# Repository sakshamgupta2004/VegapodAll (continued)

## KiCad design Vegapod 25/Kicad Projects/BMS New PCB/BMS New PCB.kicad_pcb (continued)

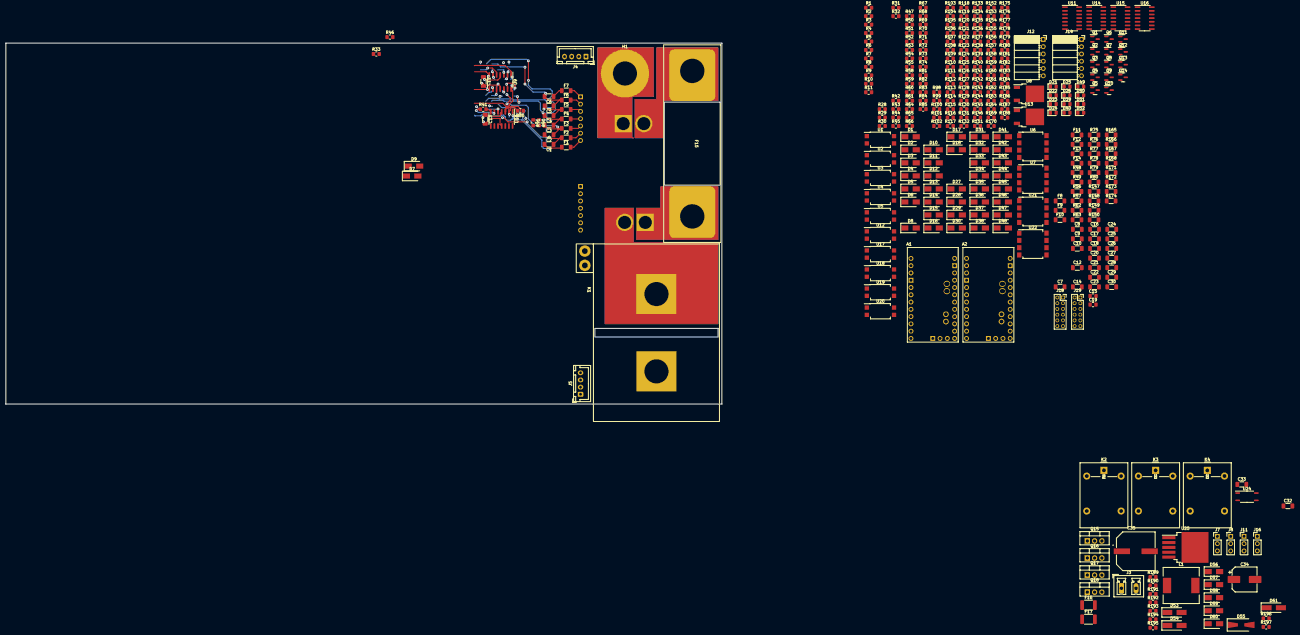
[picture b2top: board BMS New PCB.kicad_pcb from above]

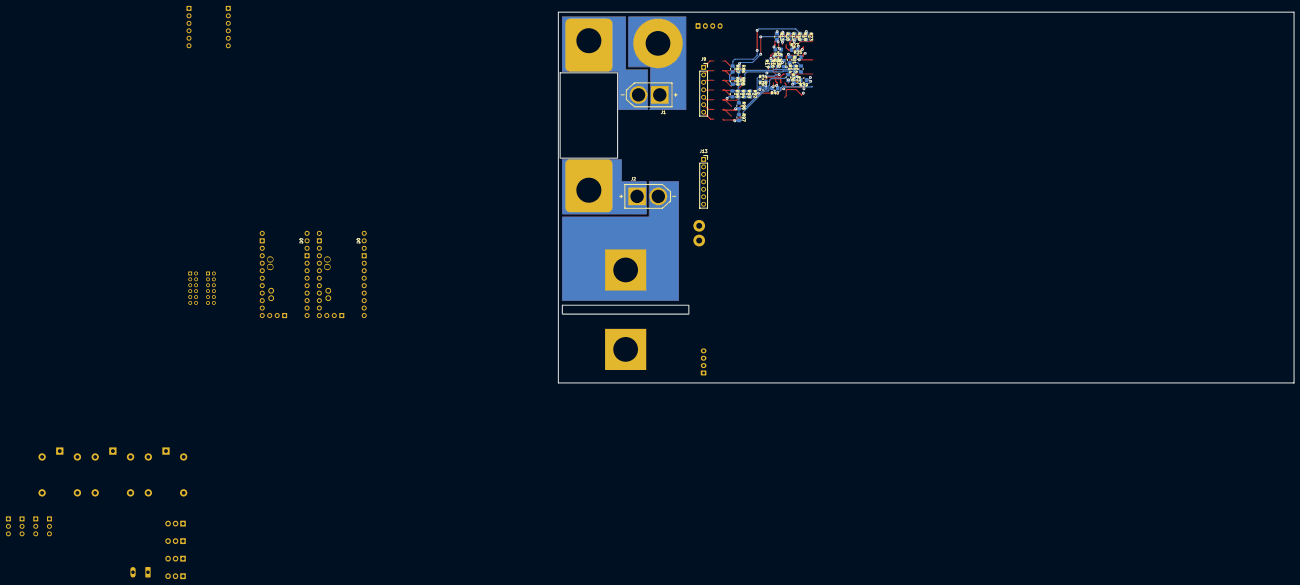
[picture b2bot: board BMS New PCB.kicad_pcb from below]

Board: 4 copper layers, 250.0 x 126.0 mm, 372 parts (36 on the bottom side), 238 nets.

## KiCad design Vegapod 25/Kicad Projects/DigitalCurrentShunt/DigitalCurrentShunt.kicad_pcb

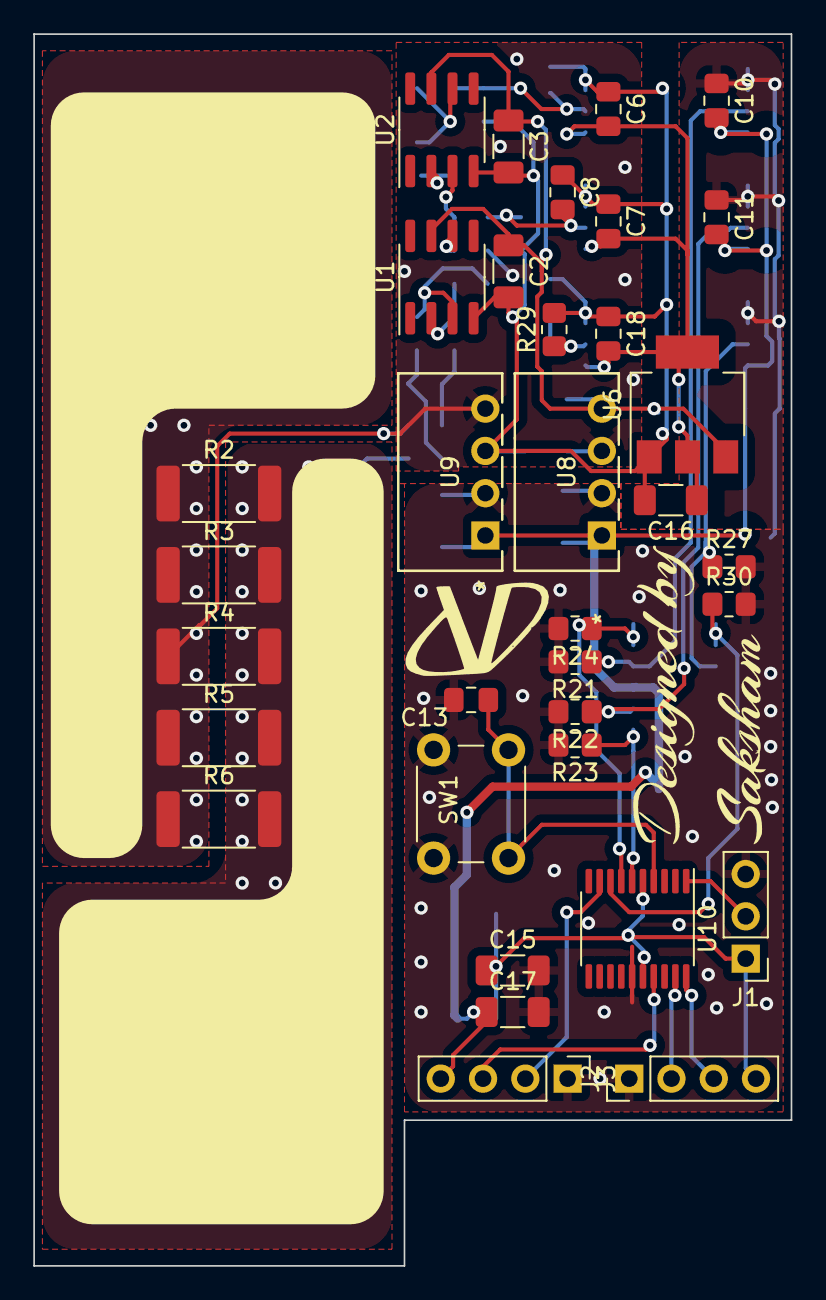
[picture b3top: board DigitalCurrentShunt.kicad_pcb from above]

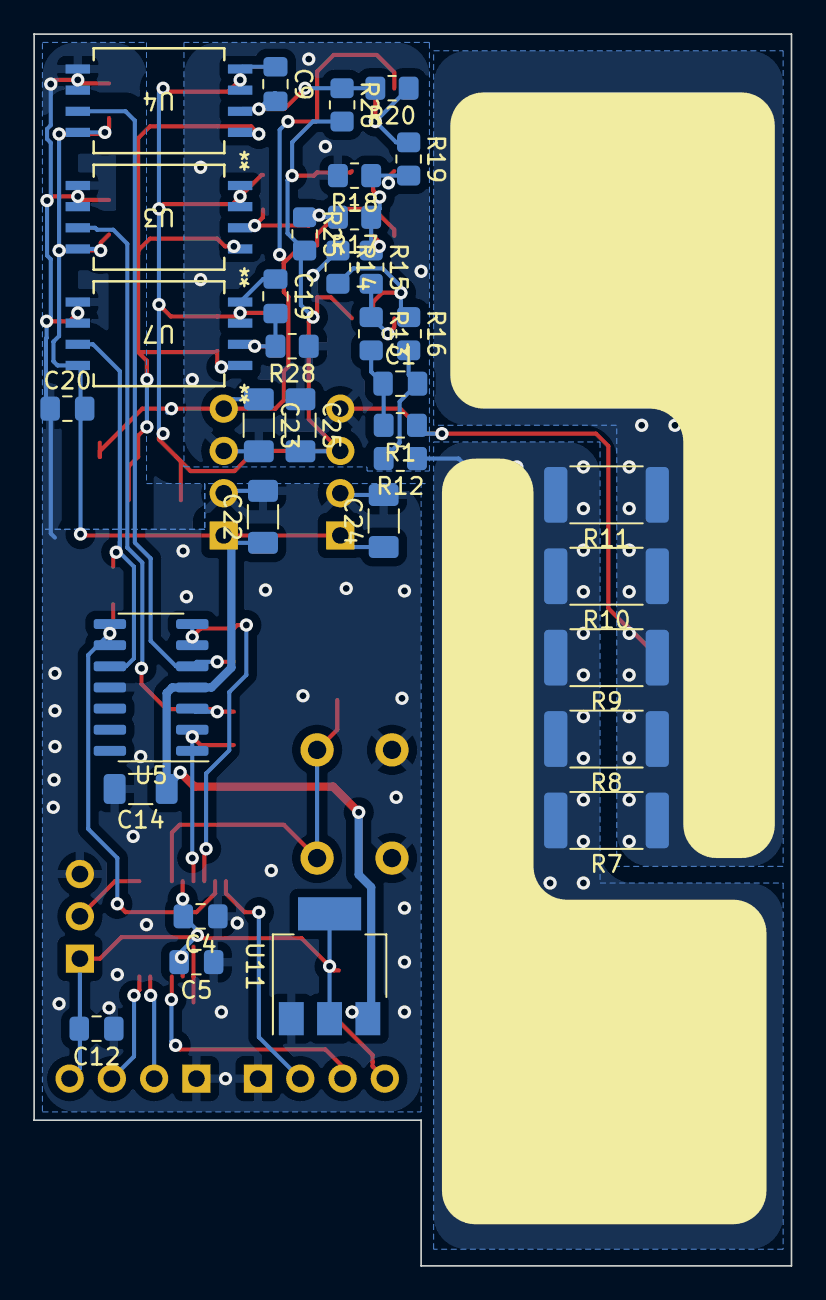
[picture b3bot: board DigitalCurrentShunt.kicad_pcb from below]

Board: 4 copper layers, 45.5 x 74.0 mm, 71 parts (35 on the bottom side), 30 nets.

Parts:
C1, C4, C5, C6, C7, C10, C11, C12, C13, C18, C20: 100n; C_0805_2012Metric_Pad1.18x1.45mm_HandSolder
C2, C3, C14, C15, C16, C17, C22, C23, C24, C25: 10uF; C_1206_3216Metric_Pad1.33x1.80mm_HandSolder
C8, C9, C19: 10n; C_0805_2012Metric_Pad1.18x1.45mm_HandSolder
J1: BootSel; PinHeader_1x03_P2.54mm_Vertical
J2: STLINK; PinHeader_1x04_P2.54mm_Vertical
J3: UART; PinHeader_1x04_P2.54mm_Vertical
MP1, MP2: 7461059; WP-BUCF_7461059
R1, R12: 47; R_0805_2012Metric_Pad1.20x1.40mm_HandSolder
R2, R3, R4, R5, R6, R7, R8, R9, R10, R11: 5mOhm; R_2512_6332Metric_Pad1.40x3.35mm_HandSolder
R13, R16, R17, R18, R20, R23, R24, R25, R26, R28, R29, R30: 470; R_0805_2012Metric_Pad1.20x1.40mm_HandSolder
R14, R15: 22k; R_0805_2012Metric_Pad1.20x1.40mm_HandSolder
R19, R21, R22, R27: 4.7k; R_0805_2012Metric_Pad1.20x1.40mm_HandSolder
SW1: SW_Push; SW_PUSH_6mm
U1, U2: OP177; SOIC-8_3.9x4.9mm_P1.27mm
U3, U4, U7: ADUM4195-1BRIZ; RI-8-1_ADI
U5: LM324; SOIC-14_3.9x8.7mm_P1.27mm
U6: AMS1117-5.0; SOT-223-3_TabPin2
U8, U9: B0505S-1WR3; B0505S_MNS
U10: STM32F030F4Px; TSSOP-20_4.4x6.5mm_P0.65mm
U11: AMS1117-3.3; SOT-223-3_TabPin2

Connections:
+3.3V: C4.2, C5.2, C12.2, C15.1, J1.1, J2.4, U10.5 (VDDA), U10.16 (VDD), U11.2 (VO)
+5V: C2.1, C3.1, C23.1, U1.7 (V+), U2.7 (V+), U6.3 (VI), U8.4 (+VO)
+5VD: C10.2, C11.2, C14.1, C17.1, C20.2, C22.1, C24.1, J3.4, U3.8 (VDD1), U4.8 (VDD1), U5.4 (V+), U7.8 (VDD1), U8.1 (GND), U9.1 (GND), U11.3 (VI)
-5V: C2.2, C3.2, C6.1, C7.1, C8.1, C9.1, C16.2, C18.1, C19.1, C25.2, R25.2, R26.2, R29.2, U1.4 (V-), U2.4 (V-), U3.3 (SHTD), U3.4 (GND2), U4.3 (SHTD), U4.4 (GND2), U6.1 (GND), U7.3 (SHTD), U7.4 (GND2), U9.3 (0V)
-BATT: C23.2, C25.1, MP1.1, R1.1, R2.1, R3.1, R4.1, R5.1, R6.1, R7.1, R8.1, R9.1, R10.1, R11.1, R14.1, R18.2, R28.1, U8.3 (0V), U9.4 (+VO)
/RST: C13.2, SW1.2, U10.4 (NRST)
A0: C8.2, R17.2, R25.1, U3.2 (VIN)
A1: C9.2, R20.2, R26.1, U4.2 (VIN)
GNDD: C4.1, C5.1, C10.1, C11.1, C12.1, C13.1, C14.2, C15.2, C17.2, C20.1, C22.2, C24.2, J1.3, J2.1, J3.1, R21.2, R22.2, R23.2, R24.2, R27.2, R30.2, SW1.1, U3.5 (GND1), U3.6 (NC), U4.5 (GND1), U4.6 (NC), U5.11 (V-), U7.5 (GND1), U7.6 (NC), U8.2 (VIN), U9.2 (VIN), U10.15 (VSS), U11.1 (GND)
unnamed: C1.1, R1.2, R13.2
unnamed: C1.2, R12.2, R16.2
unnamed: J1.2, U10.1 (BOOT0)
unnamed: MP2.1, R2.2, R3.2, R4.2, R5.2, R6.2, R7.2, R8.2, R9.2, R10.2, R11.2, R12.1
unnamed: R19.1, R20.1, U2.6
unnamed: R14.2, R16.1, U1.3 (+)
unnamed: R13.1, R15.2, U1.2 (-)
unnamed: R15.1, R17.1, U1.6, U2.3 (+)
unnamed: R18.1, R19.2, U2.2 (-)
unnamed: C6.2, C7.2, C16.1, C18.2, U3.1 (VDD2), U4.1 (VDD2), U6.2 (VO), U7.1 (VDD2)
unnamed: R22.1, U3.7 (VOUT), U5.3 (+)
unnamed: R21.1, U4.7 (VOUT), U5.5 (+)
unnamed: R27.1, U5.10 (+), U7.7 (VOUT)
unnamed: C19.2, R28.2, R29.1, U7.2 (VIN)
PA0: R23.1, U5.1, U5.2 (-), U10.6 (PA0)
PA1: R24.1, U5.6 (-), U5.7, U10.7 (PA1)
PA2: R30.1, U5.8, U5.9 (-), U10.8 (PA2)
RX: J3.2, U10.9 (PA3)
SWCLK: J2.2, U10.19 (PA13)
SWDIO: J2.3, U10.20 (PA14)
TX: J3.3, U10.17 (PA9)

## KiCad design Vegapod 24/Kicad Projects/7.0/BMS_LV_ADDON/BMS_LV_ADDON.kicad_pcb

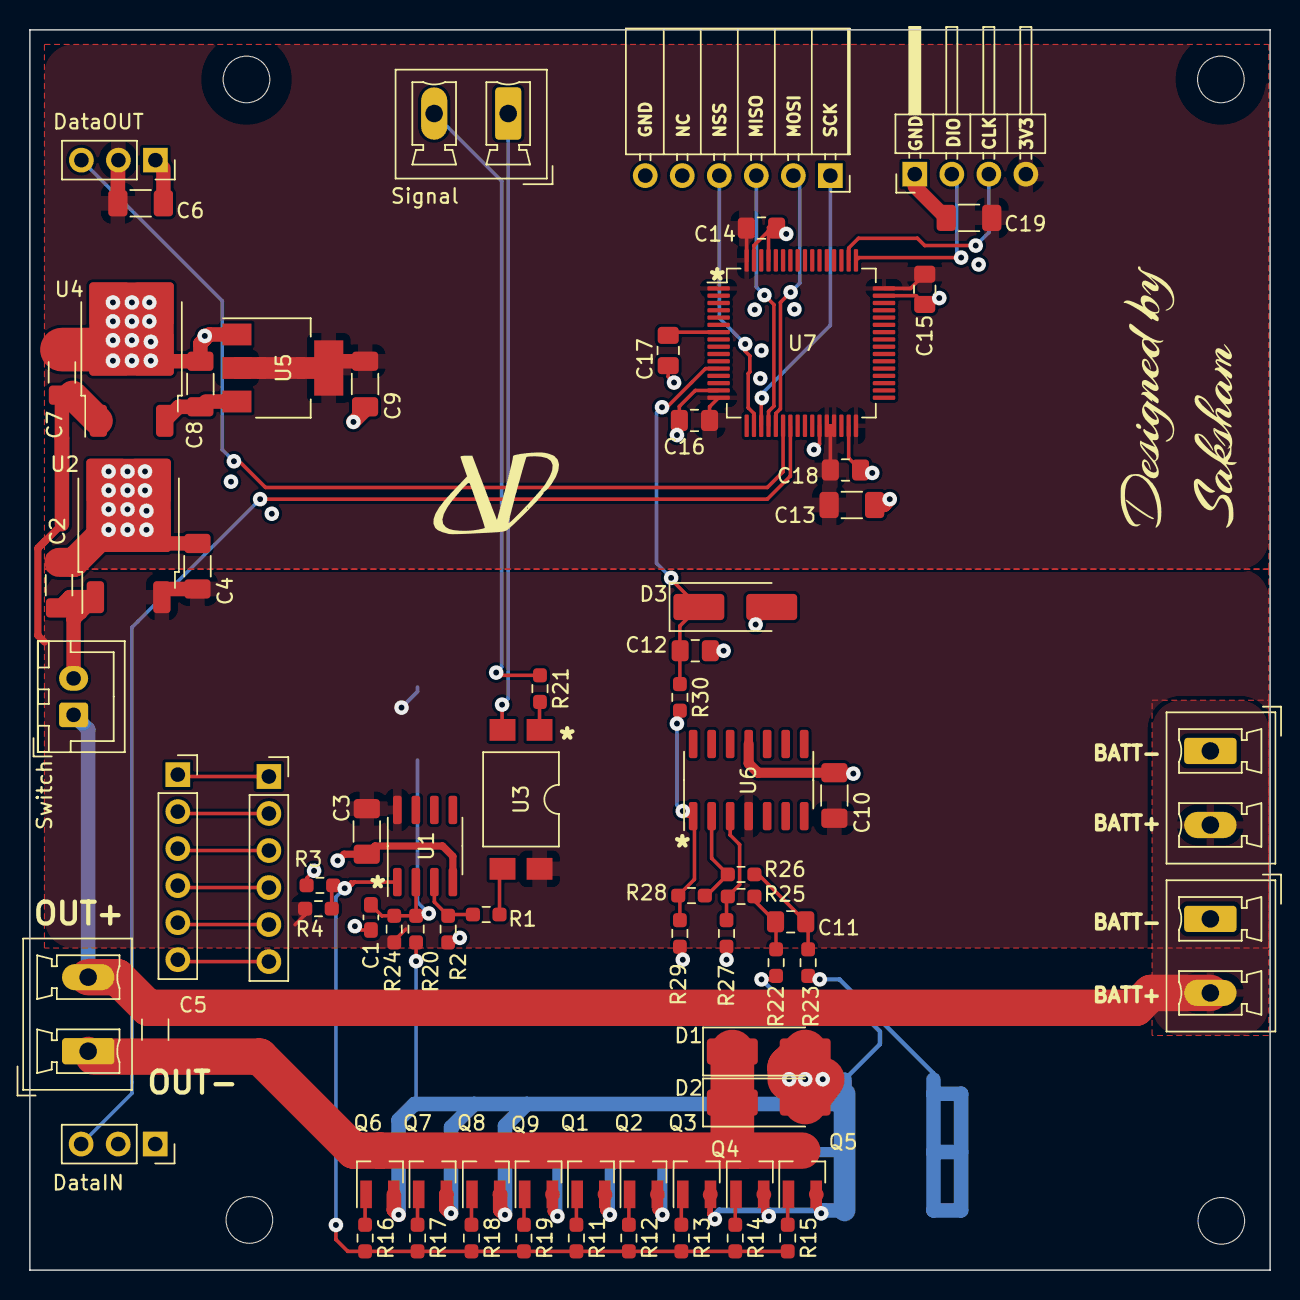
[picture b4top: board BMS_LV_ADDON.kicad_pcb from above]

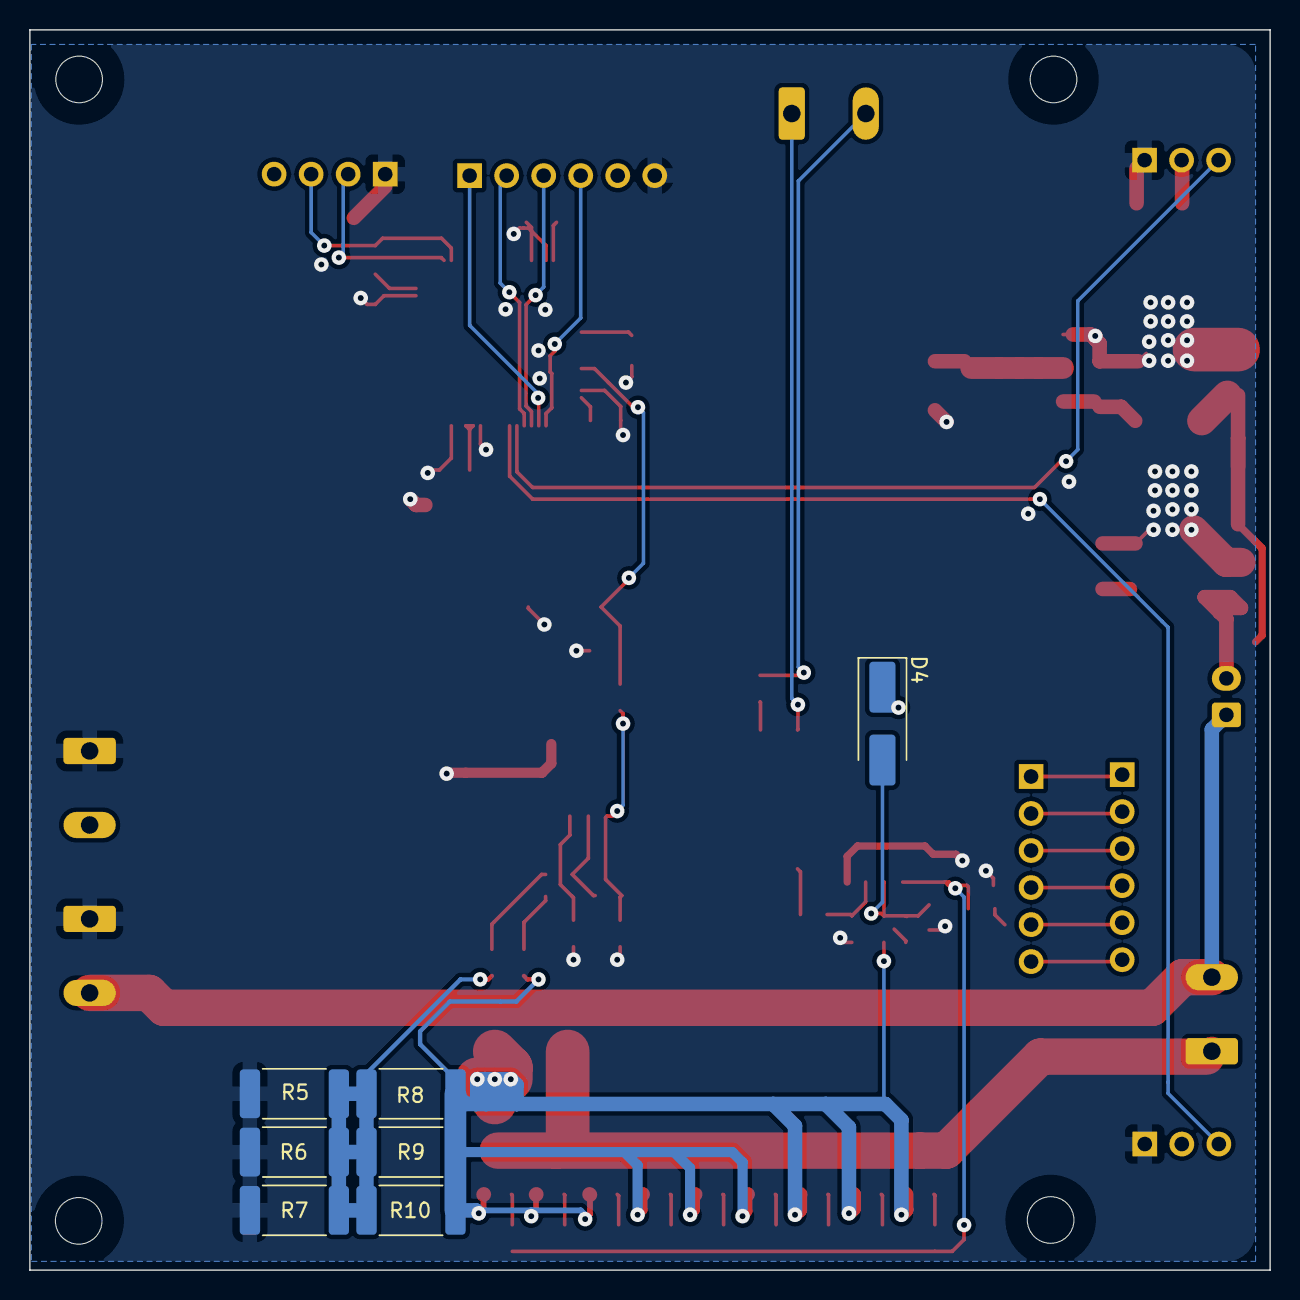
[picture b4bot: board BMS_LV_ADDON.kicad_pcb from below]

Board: 2 copper layers, 85.1 x 85.1 mm, 84 parts (7 on the bottom side), 46 nets.

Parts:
C1: Open Circuit; C_0603_1608Metric_Pad1.08x0.95mm_HandSolder
C2, C3, C4, C5, C6, C7, C8, C9, C10, C13, C19: 10u; C_1206_3216Metric_Pad1.33x1.80mm_HandSolder
C11, C12, C14, C15, C16, C17, C18: 100n; C_0805_2012Metric_Pad1.18x1.45mm_HandSolder
D1, D2, D4: US1M; D_SMA_Handsoldering
D3: 5.1v Zener Diode; D_SMA_Handsoldering
H1, H2, H3, H4: MountingHole; MountingHole_3.2mm_M3
J1, J2: Data; PinSocket_1x06_P2.54mm_Vertical
J3: DataIN; PinSocket_1x03_P2.54mm_Vertical
J4: DataOUT; PinSocket_1x03_P2.54mm_Vertical
J5, J6: Batt; PhoenixContact_MCV_1,5_2-G-5.08_1x02_P5.08mm_Vertical
J7: Switch; JST_XH_B2B-XH-A_1x02_P2.50mm_Vertical
J8: Signal; PhoenixContact_MCV_1,5_2-G-5.08_1x02_P5.08mm_Vertical
J9: OUTPUT; PhoenixContact_MCV_1,5_2-G-5.08_1x02_P5.08mm_Vertical
J10: ST-Link; PinHeader_1x04_P2.54mm_Horizontal
J11: Conn_01x06_Pin; PinSocket_1x06_P2.54mm_Horizontal
Q1, Q2, Q3, Q4, Q5, Q6, Q7, Q8, Q9: AO3400; SOT-23_Handsoldering
R1, R20, R21, R25, R26, R29: 1k; R_0603_1608Metric_Pad0.98x0.95mm_HandSolder
R2, R11, R12, R13, R14, R15, R16, R17, R18, R19, R22, R23, R30: 100; R_0603_1608Metric_Pad0.98x0.95mm_HandSolder
R3, R4, R24: 100k; R_0603_1608Metric_Pad0.98x0.95mm_HandSolder
R5, R6, R7, R8, R9, R10: 0.1; R_2512_6332Metric_Pad1.40x3.35mm_HandSolder
R27, R28: 10k; R_0603_1608Metric_Pad0.98x0.95mm_HandSolder
U1: LM393; SOIC-8_3.9x4.9mm_P1.27mm
U2: 78M15; TO-252-2
U3: EL814; SMDIP-4_W9.53mm_Clearance8mm
U4: 78M05; TO-252-2
U5: AMS1117-3.3; SOT-223-3_TabPin2
U6: LM324; SOIC-14_3.9x8.7mm_P1.27mm
U7: STM32G474RETx; LQFP-64_10x10mm_P0.5mm

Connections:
+3.3V: C6.1, C9.1, C13.1, C14.1, C15.1, C16.1, C18.1, C19.2, J4.2, J10.4, U5.2 (VO), U7.1 (VBAT), U7.16 (VDD), U7.28 (VREF+), U7.29 (VDDA), U7.32 (VDD), U7.48 (VDD), U7.64 (VDD)
+5V: C8.1, U4.3 (VO), U5.3 (VI)
+15V: C3.1, C4.1, C7.1, C10.1, D4.1 (K), R4.2, R24.1, U1.8 (V+), U2.3 (VO), U3.4, U4.1 (VI), U6.4 (V+)
+BATT: C5.1, J5.2, J6.2, J7.1, J9.2
-BATT: C1.2, C2.2, C3.2, C4.2, C6.2, C7.2, C8.2, C9.2, C10.2, C12.2, C13.2, C14.2, C15.2, C16.2, C17.2, C18.2, C19.1, D3.2 (A), J3.1, J4.1, J5.1, J6.1, J10.1, J11.6, R2.1, R3.1, R5.1, R6.1, R7.1, R27.1, R29.1, U1.4 (V-), U2.2 (GND), U4.2 (GND), U5.1 (GND), U6.11 (V-), U7.15 (VSS), U7.27 (VSSA), U7.31 (VSS), U7.47 (VSS), U7.61 (PB8), U7.63 (VSS)
A0: C12.1, D3.1 (K), R30.1, U7.12 (PA0)
DIN: J3.3, U7.23 (PC5)
DOUT: J4.3, U7.22 (PC4)
Gate: R3.2, R4.1, R11.2, R12.2, R13.2, R14.2, R15.2, R16.2, R17.2, R18.2, R19.2, U1.1
MISO: J11.3, U7.20 (PA6)
MOSI: J11.2, U7.21 (PA7)
NSS: J11.4, U7.18 (PA4)
unnamed: C11.1, R22.1, R25.2
unnamed: C11.2, R23.1, R26.2
unnamed: C5.2, D1.1 (K), D2.1 (K), J9.1, Q1.3 (C), Q2.3 (C), Q3.3 (C), Q4.3 (C), Q5.3 (C), Q6.3 (C), Q7.3 (C), Q8.3 (C), Q9.3 (C)
unnamed: C1.1, D4.2 (A), R20.2, R24.2, U1.2 (-)
unnamed: J1.1, J2.1
unnamed: J1.2, J2.2
unnamed: J1.3, J2.3
unnamed: J1.4, J2.4
unnamed: J1.5, J2.5
unnamed: J1.6, J2.6
unnamed: C2.1, J7.2, U2.1 (VI)
unnamed: J8.1, U3.2
unnamed: J8.2, R21.1
unnamed: Q1.1 (B), R11.1
unnamed: Q2.1 (B), R12.1
unnamed: Q3.1 (B), R13.1
unnamed: Q4.1 (B), R14.1
unnamed: Q5.1 (B), R15.1
unnamed: Q6.1 (B), R16.1
unnamed: Q7.1 (B), R17.1
unnamed: Q8.1 (B), R18.1
unnamed: Q9.1 (B), R19.1
unnamed: R1.1, U3.3
unnamed: R21.2, U3.1
unnamed: R28.2, R29.2, R30.2, U6.1
unnamed: R1.2, R2.2, U1.3 (+)
unnamed: R25.1, R27.2, U6.3 (+)
unnamed: R26.1, R28.1, U6.2 (-)
unnamed: C17.1, U7.7 (PG10)
SCK: J11.1, U7.19 (PA5)
SHUNT+: D1.2 (A), D2.2 (A), Q1.2 (E), Q2.2 (E), Q3.2 (E), Q4.2 (E), Q5.2 (E), Q6.2 (E), Q7.2 (E), Q8.2 (E), Q9.2 (E), R8.2, R9.2, R10.2, R20.1, R22.2
SHUNT-: R5.2, R6.2, R7.2, R8.1, R9.1, R10.1, R23.2
SWCLK: J10.3, U7.50 (PA14)
SWDIO: J10.2, U7.49 (PA13)

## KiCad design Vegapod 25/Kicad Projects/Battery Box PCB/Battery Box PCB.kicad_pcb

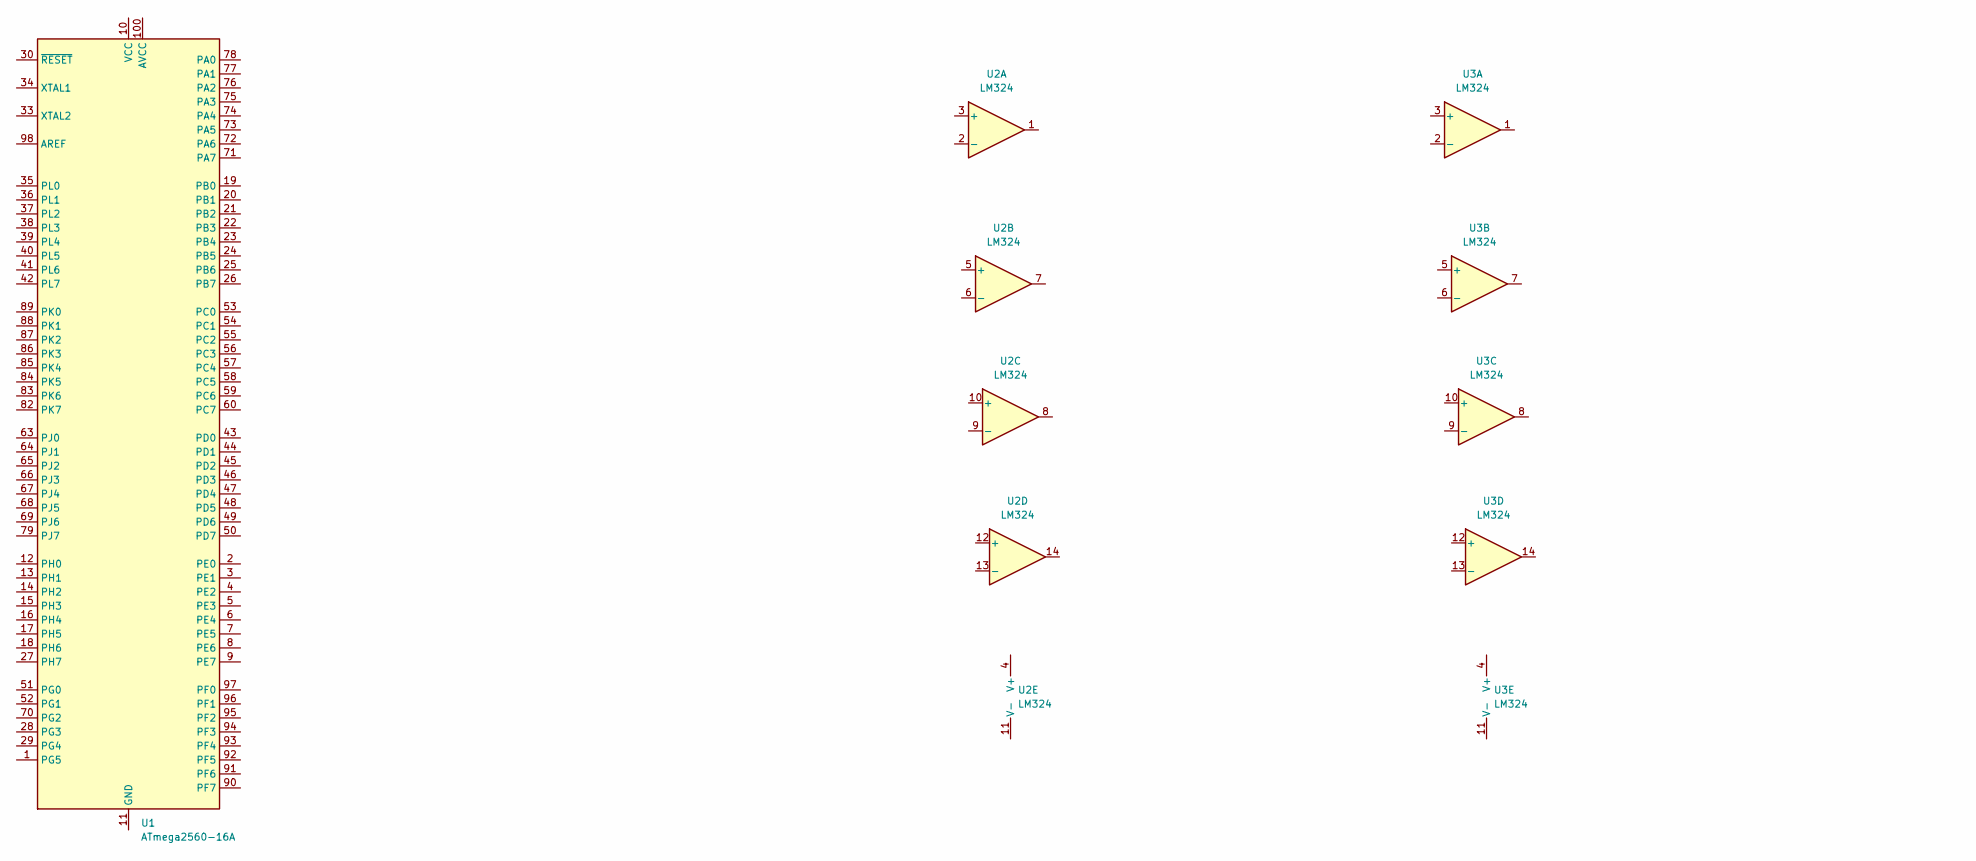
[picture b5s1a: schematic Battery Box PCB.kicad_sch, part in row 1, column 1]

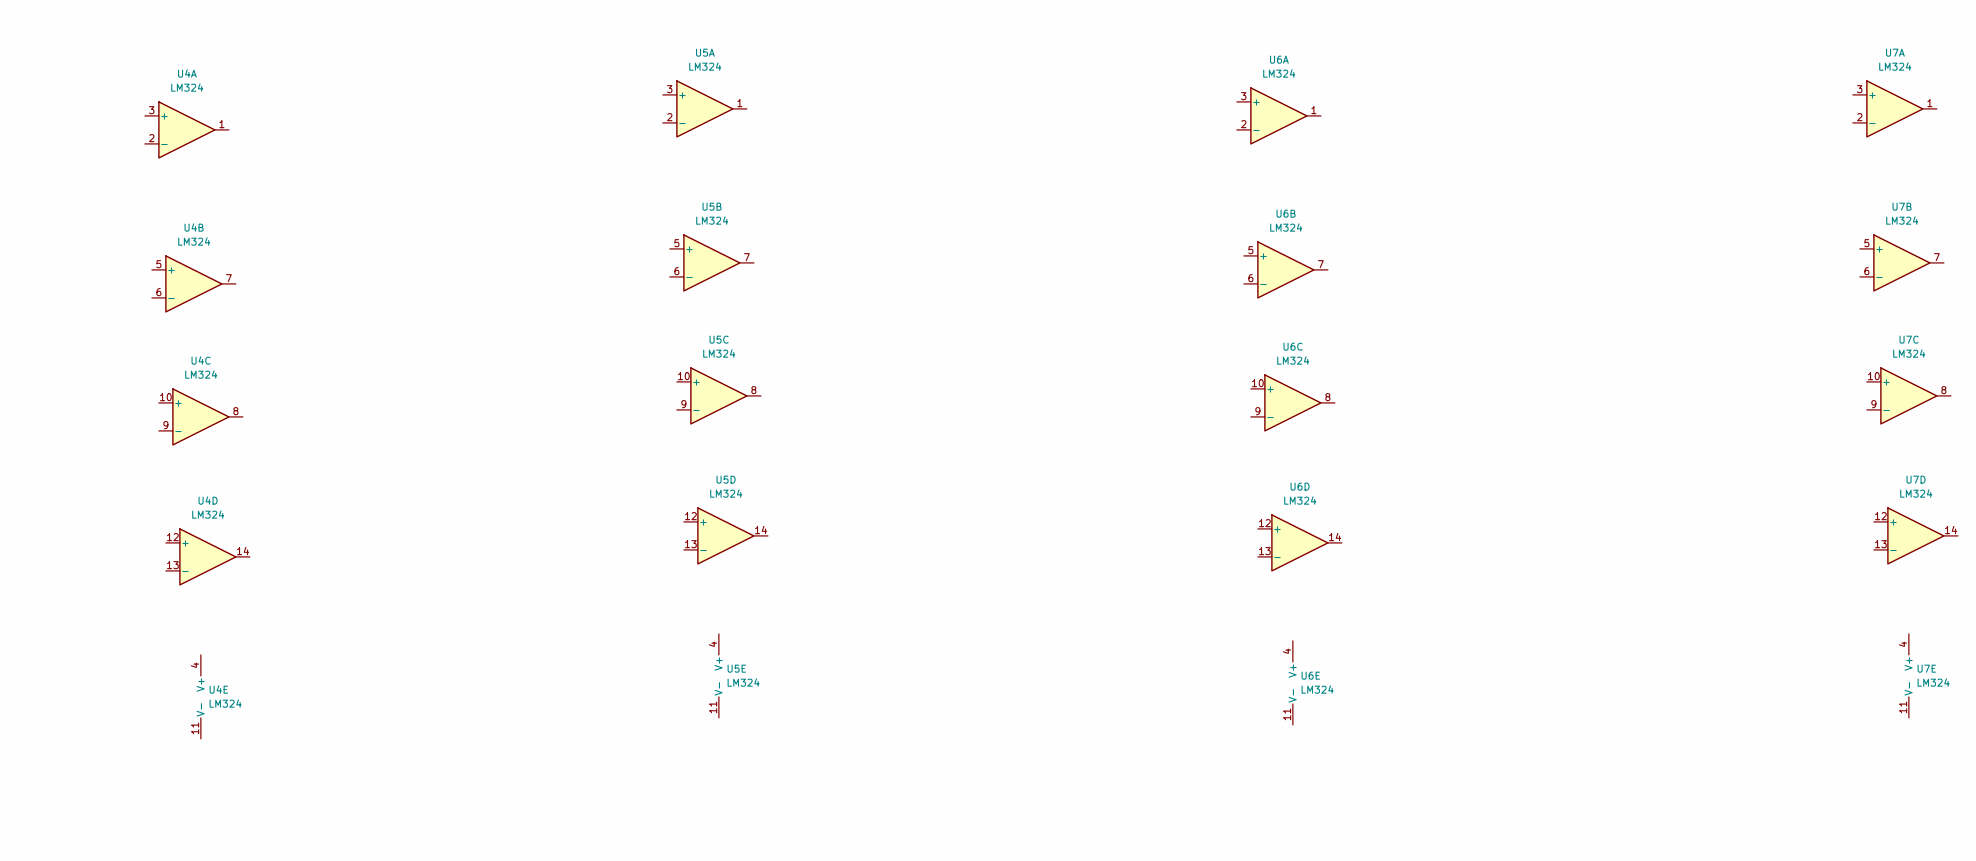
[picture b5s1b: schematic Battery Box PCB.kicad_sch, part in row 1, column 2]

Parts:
U1: ATmega2560-16A; TQFP-100_14x14mm_P0.5mm
U2, U3, U4, U5, U6, U7: LM324; TSSOP-14_4.4x5mm_P0.65mm

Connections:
unnamed: U1.11 (GND), U1.32 (GND), U1.62 (GND), U1.81 (GND), U1.99 (GND)
unnamed: U1.10 (VCC), U1.31 (VCC), U1.61 (VCC), U1.80 (VCC)

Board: 2 copper layers, 7 parts (0 on the bottom side), 2 nets, no tracks yet.

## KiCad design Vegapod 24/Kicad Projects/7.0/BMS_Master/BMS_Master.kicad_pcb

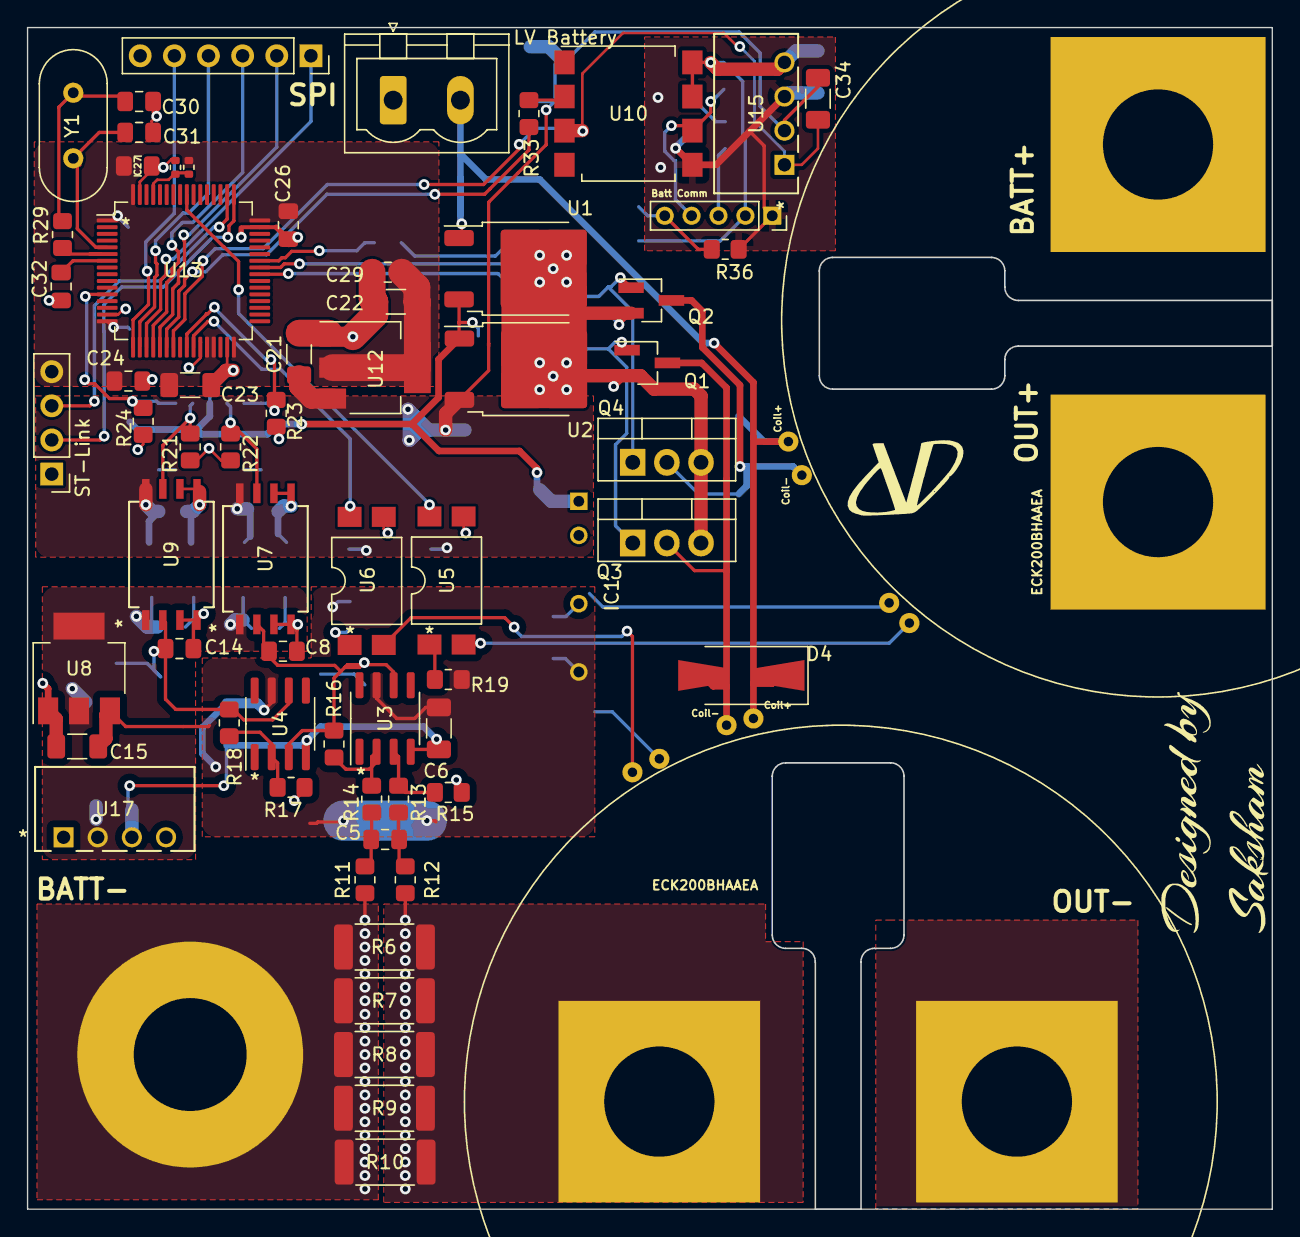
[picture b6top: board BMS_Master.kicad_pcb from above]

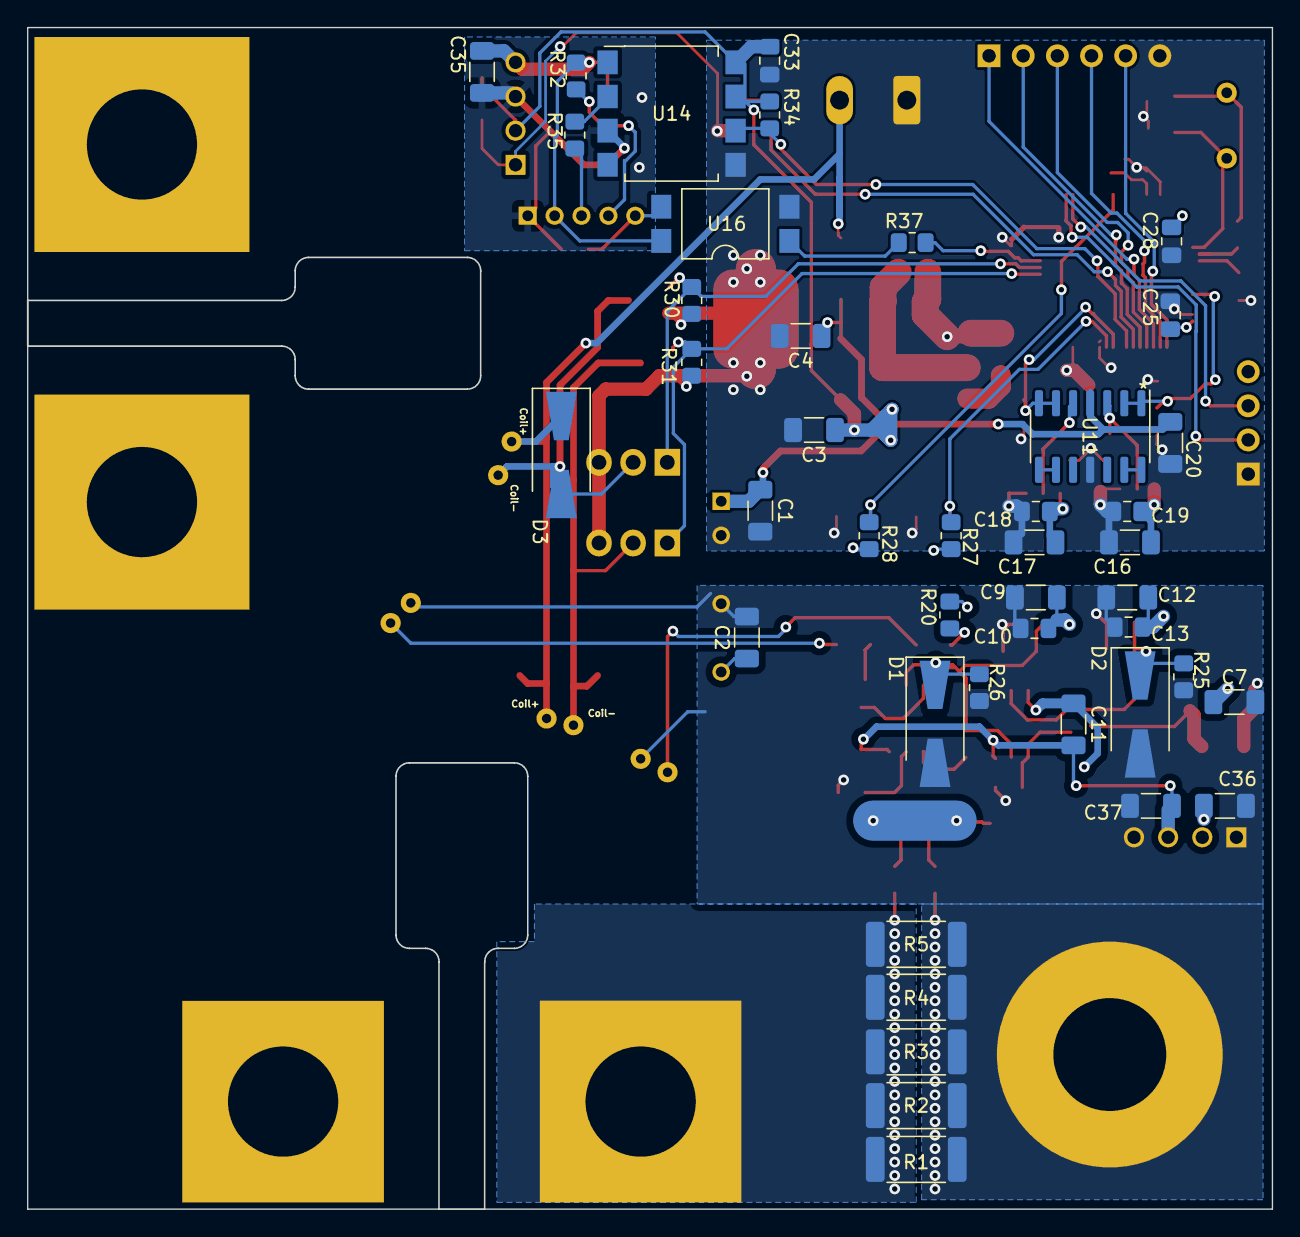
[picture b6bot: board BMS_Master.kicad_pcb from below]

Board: 2 copper layers, 92.6 x 87.9 mm, 110 parts (43 on the bottom side), 56 nets.

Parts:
C1, C2, C3, C4, C6, C7, C9, C11, C12, C15, C16, C17, C20, C21, C22, C23, C34, C35, C36, C37: 10uF; C_1206_3216Metric_Pad1.33x1.80mm_HandSolder
C5, C10, C13, C18, C19, C24, C25, C26, C27, C28, C29, C32, C33: 100n; C_0805_2012Metric_Pad1.18x1.45mm_HandSolder
C8, C14: 10n; C_0805_2012Metric_Pad1.18x1.45mm_HandSolder
C30, C31: 22p; C_0805_2012Metric_Pad1.18x1.45mm_HandSolder
D1, D2: Zener-5.1V; D_SMA-SMB_Universal_Handsoldering
D3, D4: US1m; D_SMA-SMB_Universal_Handsoldering
H1: BATT-; MountingHole_8.4mm_M8_Pad
IC1: B0505S-2W
J1: LV Battery; PhoenixContact_MSTBVA_2,5_2-G_1x02_P5.00mm_Vertical
J2: ST-Link; PinHeader_1x04_P2.54mm_Vertical
J3: Conn_01x06_Pin; PinSocket_1x06_P2.54mm_Vertical
J4: Batt Comm; PinSocket_1x05_P2.00mm_Vertical
K1, K2: ECK200BHAAEA
Q1, Q2: SI2318CDS (SI2318); SOT-23_Handsoldering
Q3, Q4: IRLZ44N; TO-220-3_Vertical
R1, R2, R3, R4, R5, R6, R7, R8, R9, R10: 5mOhm; R_2512_6332Metric_Pad1.40x3.35mm_HandSolder
R11, R12: 10; R_0805_2012Metric_Pad1.20x1.40mm_HandSolder
R13, R14, R17, R23, R24, R25, R26, R27, R28, R30, R31, R32, R33, R34, R35, R36, R37: 470; R_0805_2012Metric_Pad1.20x1.40mm_HandSolder
R15, R16, R18: 22k; R_0805_2012Metric_Pad1.20x1.40mm_HandSolder
R19, R20: 1k; R_0805_2012Metric_Pad1.20x1.40mm_HandSolder
R21, R22: 4.7k; R_0805_2012Metric_Pad1.20x1.40mm_HandSolder
R29: 10k; R_0805_2012Metric_Pad1.20x1.40mm_HandSolder
R38: Open Circuit; R_0402_1005Metric
R39: SHORT OUT; R_0402_1005Metric
U1: KA78M12_TO252; TO-252-2
U2: KA78M05_TO252; TO-252-2
U3, U4: OP177; SOIC-8_3.9x4.9mm_P1.27mm
U5, U6, U16: EL814; SMDIP-4_W9.53mm_Clearance8mm
U7, U9: ADUM4195-1BRIZ; RI-8-1_ADI
U8: AMS1117-5.0; SOT-223-3_TabPin2
U10, U14: 6N137; SSO-8_6.7x9.8mm_P2.54mm_Clearance8mm
U11: LM324; SOIC-14_3.9x8.7mm_P1.27mm
U12: AMS1117-3.3; SOT-223-3_TabPin2
U13: STM32G474RETx; LQFP-64_10x10mm_P0.5mm
U15, U17: B0505S-1WR3; B0505S_MNS
Y1: Crystal; Crystal_HC49-U_Vertical

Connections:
+3.3V: C22.1, C23.1, C24.2, C25.2, C26.2, C27.2, C28.2, C29.2, J2.4, R38.2, U12.2 (VO), U13.1 (VBAT), U13.16 (VDD), U13.28 (VREF+), U13.29 (VDDA), U13.32 (VDD), U13.48 (VDD), U13.64 (VDD)
+5V: C7.1, C9.1, C10.2, C12.1, C13.2, C36.2, U7.1 (VDD2), U8.2 (VO), U9.1 (VDD2), U17.2 (VIN)
+5VD: C3.1, C16.1, C17.1, C18.2, C19.2, C21.1, C33.2, C34.1, R27.1, R28.1, R34.2, U2.3 (VO), U7.8 (VDD1), U9.8 (VDD1), U12.3 (VI), U14.7 (EN), U14.8 (VCC), U15.2 (VIN)
+12V: C2.1, C6.1, C11.1, C15.1, IC1.VOUT, R19.2, R20.2, U3.7 (V+), U4.7 (V+), U8.3 (VI)
-5V: C6.2, C11.2, C37.2, U3.4 (V-), U4.4 (V-), U17.3 (0V)
-BATT: C2.2, C7.2, C8.1, C9.2, C10.1, C12.2, C13.1, C14.1, C15.2, C36.1, C37.1, D1.2 (A), D2.2 (A), H1.1, IC1.GNDB, K1.4 (ContactA2), K2.4 (ContactA2), R1.1, R2.1, R3.1, R4.1, R5.1, R6.1, R7.1, R8.1, R9.1, R10.1, R11.1, R15.1, R17.2, R25.2, R26.2, U7.3 (SHTD), U7.4 (GND2), U8.1 (GND), U9.3 (SHTD), U9.4 (GND2), U17.1 (GND), U17.4 (+VO)
A0: C8.2, D1.1 (K), R16.1, R26.1, U3.6, U4.3 (+), U7.2 (VIN)
A1: C14.2, D2.1 (K), R18.1, R25.1, U4.6, U9.2 (VIN)
CTRL: J3.5, U13.17 (PA3)
GND1: C35.2, J4.1, R36.2, U10.5 (GND), U14.3 (C), U15.3 (0V)
LV+: D3.1 (K), D4.1 (K), J1.2, K1.2 (Coil2), K2.2 (Coil2), U1.1 (VI)
LV-: C1.2, C3.2, C4.2, C16.2, C17.2, C18.1, C19.1, C20.2, C21.2, C22.2, C23.2, C24.1, C25.1, C26.1, C27.1, C28.1, C29.1, C30.2, C31.2, C32.2, C33.1, C34.2, IC1.GNDA, J1.1, J2.1, J3.6, Q1.2 (S), Q2.2 (S), Q3.3 (S), Q4.3 (S), R21.2, R22.2, R23.2, R24.2, R30.2, R31.2, R39.1, U1.2 (GND), U2.2 (GND), U5.3, U6.3, U7.5 (GND1), U7.6 (NC), U9.5 (GND1), U9.6 (NC), U10.3 (C), U11.11 (V-), U12.1 (GND), U13.15 (VSS), U13.27 (VSSA), U13.31 (VSS), U13.47 (VSS), U13.63 (VSS), U14.5 (GND), U15.1 (GND), U16.2
MISO: J3.3, U13.20 (PA6)
MOSI: J3.2, U13.21 (PA7)
NSS: J3.4, U13.18 (PA4)
unnamed: C5.1, R11.2, R14.2
unnamed: C5.2, R12.2, R13.2
unnamed: C30.1, R29.1, Y1.1
unnamed: D3.2 (A), K2.1 (Coil1), Q2.3 (D), Q4.2 (D)
unnamed: D4.2 (A), K1.1 (Coil1), Q1.3 (D), Q3.2 (D)
unnamed: C35.1, J4.2, R32.2, U10.7 (EN), U10.8 (VCC), U15.4 (+VO), U16.4
unnamed: J4.3, R35.1
unnamed: J4.4, R32.1, U10.6 (VO)
unnamed: J4.5, R36.1, U16.3
unnamed: K1.3 (ContactA1), U6.2
unnamed: K1.5 (ContactMain1), R1.2, R2.2, R3.2, R4.2, R5.2, R6.2, R7.2, R8.2, R9.2, R10.2, R12.1
unnamed: K2.3 (ContactA1), U5.2
unnamed: R19.1, U5.1
unnamed: R20.1, U6.1
unnamed: R37.1, U16.1
unnamed: R13.1, R15.2, U3.3 (+)
unnamed: R14.1, R16.2, U3.2 (-)
unnamed: R17.1, R18.2, U4.2 (-)
unnamed: R33.1, U10.2 (A)
unnamed: R21.1, U9.7 (VOUT), U11.3 (+)
unnamed: R22.1, U7.7 (VOUT), U11.5 (+)
unnamed: U11.8, U11.9 (-)
unnamed: U11.13 (-), U11.14
unnamed: R38.1, R39.2, U13.61 (PB8)
unnamed: C31.1, U13.5 (PF0), Y1.2
unnamed: R29.2, U13.6 (PF1)
unnamed: C32.1, U13.7 (PG10)
unnamed: R35.2, U14.2 (A)
PA0: R24.1, U11.1, U11.2 (-), U13.12 (PA0)
PA8: R37.2, U13.42 (PA8)
PB1: R23.1, U11.6 (-), U11.7, U13.25 (PB1)
PB2: R27.2, U6.4, U13.26 (PB2)
PB3: R28.2, U5.4, U13.56 (PB3)
PC8: Q1.1 (G), Q3.1 (G), R31.1, U13.40 (PC8)
PC9: Q2.1 (G), Q4.1 (G), R30.1, U13.41 (PC9)
RX: R34.1, U13.23 (PC5), U14.6 (VO)
SCK: J3.1, U13.19 (PA5)
SWCLK: J2.3, U13.50 (PA14)
SWDIO: J2.2, U13.49 (PA13)
TX: R33.2, U13.22 (PC4)
VD: C1.1, C4.1, C20.1, IC1.VIN, U1.3 (VO), U2.1 (VI), U11.4 (V+)
